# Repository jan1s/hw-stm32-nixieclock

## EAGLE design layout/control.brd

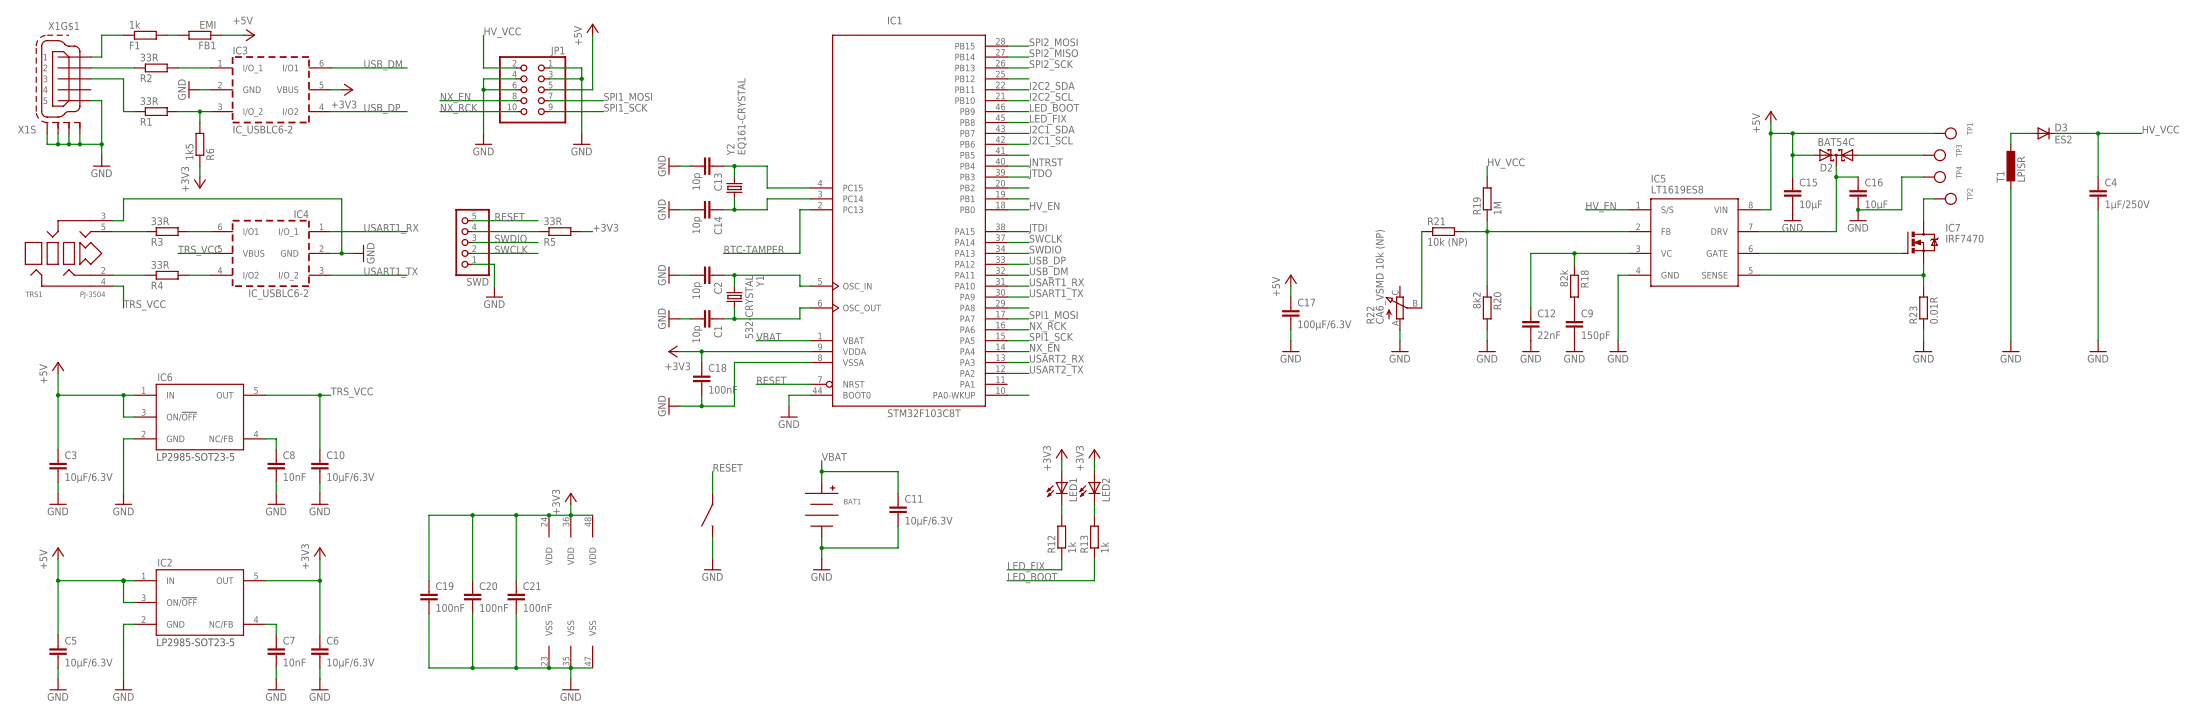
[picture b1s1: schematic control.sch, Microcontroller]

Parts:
BAT1: CR1220-HOLDER; HARWIN-CR1220
C1, C2, C13, C14: 10p; C0603
C3, C5, C6, C10, C11: 10µF/6.3V; C0603
C4: 1µF/250V; C2220K
C7, C8: 10nF; C0603
C9: 150pF; C0603
C12: 22nF; C0603
C15, C16: 10µF; C0603
C17: 100µF/6.3V; C1210
C18, C19, C20, C21: 100nF; C0603
D2: BAT54C; SOT23
D3: ES2; DO-214AA
F1: 1k; R0603
FB1: EMI; R0603
IC1: STM32F103C8T; LQFP48
IC2, IC6: LP2985-SOT23-5; SOT23-5
IC3, IC4: IC_USBLC6-2; SOT-23-6L
IC5: LT1619ES8; SO8
IC7: IRF7470; SO8
ISP: TACT-SWITCH-40-40; 40-40
JP1: PINHD-2X5_2.54-SMD; 2X05SMD
LED1, LED2: LEDCHIP-LED0603; CHIP-LED0603
R1, R2, R3, R4, R5: 33R; R0603
R6: 1k5; R0603
R12, R13: 1k; R0603
R18: 82k; R0603
R19: 1M; M1206
R20: 8k2; R0603
R21: 10k (NP); R0603
R22: CA6_VSMD 10k (NP); CA6-VSMD
R23: 0.01R; R1206
SWD: HEADER-1X5ROUND; 1X05_ROUND
T1: LPISR; PISR
TP1, TP2, TP3, TP4: TESTPOINTROUND2MM; TESTPOINT_ROUND_2MM
TRS1: PJ-3504; YD-PJ-3504
X1: MINI-USB-SCHIELD-32005-201; 32005-201
Y1: 532-CRYSTAL; 2PIN50X32
Y2: EQ161-CRYSTAL; EQ161

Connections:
+3V3: C6.1, C18.1, C19.1, C20.1, C21.1, IC1.9 (VDDA), IC1.24 (VDD), IC1.36 (VDD), IC1.48 (VDD), IC2.5 (OUT), IC3.5 (VBUS), LED1.A, LED2.A, R5.2, R6.1
+5V: C3.1, C5.1, C15.1, C17.1, D2.2 (A2), FB1.1, IC2.1 (IN), IC2.3 (ON/!OFF), IC5.8 (VIN), IC6.1 (IN), IC6.3 (ON/!OFF), JP1.5, TP1.P$1
ASDAWJIODJA: R5.1, SWD.4
GND: BAT1.NEG, C1.2, C2.2, C3.2, C4.2, C5.2, C6.2, C7.2, C8.2, C9.2, C10.2, C11.2, C12.2, C13.2, C14.2, C15.2, C16.2, C17.2, C18.2, C19.2, C20.2, C21.2, IC1.8 (VSSA), IC1.23 (VSS), IC1.35 (VSS), IC1.44 (BOOT0), IC1.47 (VSS), IC2.2 (GND), IC3.2 (GND), IC4.2 (GND), IC5.4 (GND), IC6.2 (GND), ISP.1, ISP.2, JP1.1, JP1.3, JP1.4, JP1.6, R20.2, R22.A, R23.1, SWD.1, T1.P$2 (2), TP4.P$1, TRS1.3, X1.5, X1.M1 (S1), X1.M2 (S2), X1.M3 (S3), X1.M4 (S4)
HV_EN: IC1.18 (PB0), IC5.1 (S/S)
HV_VCC: C4.1, D3.C, JP1.2, R19.2
I2C1_SCL: IC1.42 (PB6)
I2C1_SDA: IC1.43 (PB7)
I2C2_SCL: IC1.21 (PB10)
I2C2_SDA: IC1.22 (PB11)
JNTRST: IC1.40 (PB4)
JTDI: IC1.38 (PA15)
JTDO: IC1.39 (PB3)
LED_BOOT: IC1.46 (PB9), R13.1
LED_FIX: IC1.45 (PB8), R12.1
unnamed: C1.1, IC1.6 (OSC_OUT), Y1.P$1 (1)
unnamed: C2.1, IC1.5 (OSC_IN), Y1.P$2 (2)
unnamed: F1.1, X1.1
unnamed: C8.1, IC6.4 (NC/FB)
unnamed: IC3.3 (I/O_2), R1.2, R6.2
unnamed: IC4.6 (I/O1), R3.2
unnamed: D2.1 (A1), TP3.P$1
unnamed: IC5.6 (GATE), IC7.4 (G)
unnamed: LED2.C, R13.2
unnamed: LED1.C, R12.2
unnamed: R4.1, TRS1.2
unnamed: IC7.5 (D), IC7.6 (D), IC7.7 (D), IC7.8 (D), TP2.P$1
unnamed: C12.1, IC5.3 (VC), R18.1
unnamed: C9.1, R18.2
unnamed: D3.A, T1.P$1 (1)
unnamed: IC5.2 (FB), R19.1, R20.1, R21.2
unnamed: IC5.5 (SENSE), IC7.1 (S), IC7.2 (S), IC7.3 (S), R23.2
unnamed: C16.1, D2.3 (CC), IC5.7 (DRV)
unnamed: C7.1, IC2.4 (NC/FB)
unnamed: R21.1, R22.B (S)
unnamed: F1.2, FB1.2
unnamed: IC3.1 (I/O_1), R2.2
unnamed: R2.1, X1.2
unnamed: IC4.4 (I/O2), R4.2
unnamed: R3.1, TRS1.5
unnamed: C13.1, IC1.4 (PC15), Y2.P$1 (1)
unnamed: C14.1, IC1.3 (PC14), Y2.P$2 (2)
unnamed: R1.1, X1.3
NX_EN: IC1.14 (PA4), JP1.8
NX_RCK: IC1.16 (PA6), JP1.10
RESET: IC1.7 (NRST), ISP.3, ISP.4, SWD.5
RTC-TAMPER: IC1.2 (PC13)
SPI1_MOSI: IC1.17 (PA7), JP1.7
SPI1_SCK: IC1.15 (PA5), JP1.9
SPI2_MISO: IC1.27 (PB14)
SPI2_MOSI: IC1.28 (PB15)
SPI2_SCK: IC1.26 (PB13)
SWCLK: IC1.37 (PA14), SWD.2
SWDIO: IC1.34 (PA13), SWD.3
TRS_VCC: C10.1, IC4.5 (VBUS), IC6.5 (OUT), TRS1.4
USART1_RX: IC1.31 (PA10), IC4.1 (I/O_1)
USART1_TX: IC1.30 (PA9), IC4.3 (I/O_2)
USART2_RX: IC1.13 (PA3)
USART2_TX: IC1.12 (PA2)
USB_DM: IC1.32 (PA11), IC3.6 (I/O1)
USB_DP: IC1.33 (PA12), IC3.4 (I/O2)
VBAT: BAT1.POS, C11.1, IC1.1 (VBAT)

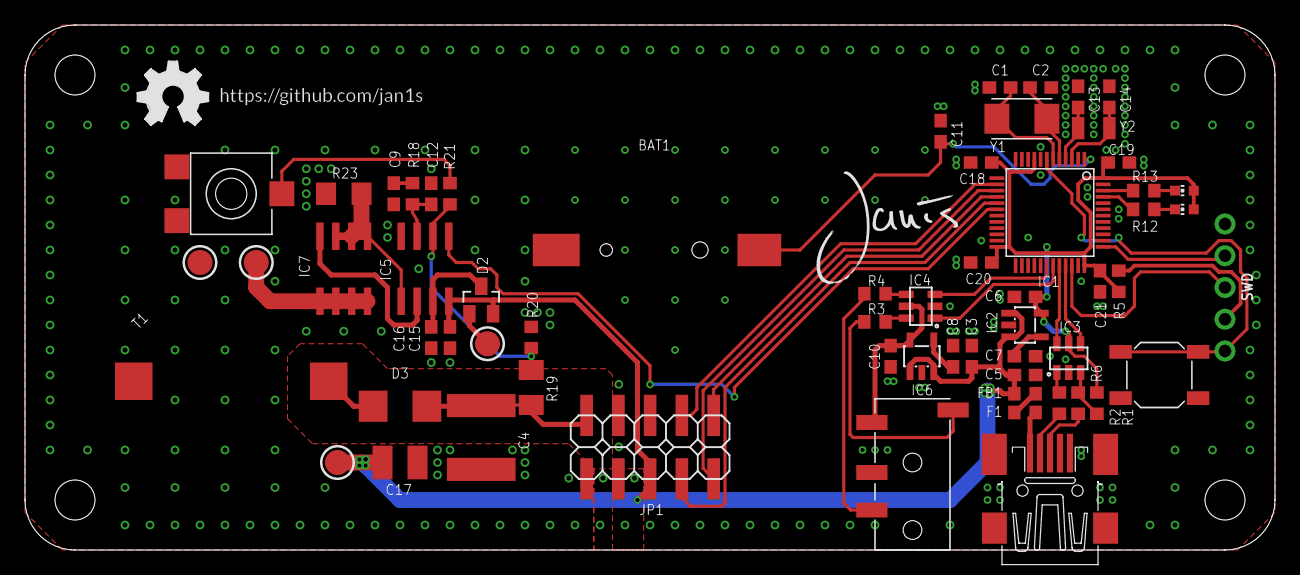
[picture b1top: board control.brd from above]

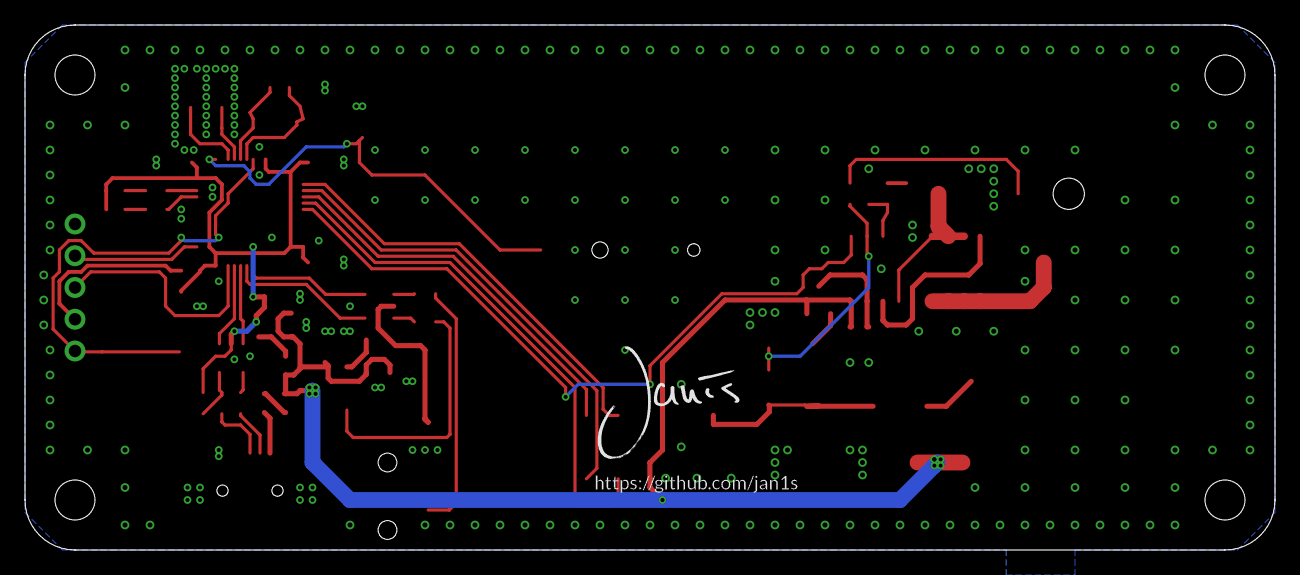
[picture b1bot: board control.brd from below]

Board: 2 copper layers, 100.0 x 42.0 mm, 66 parts (2 on the bottom side), 49 nets.

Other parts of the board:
LOGO1: OSHW_LOGO_FILLX0200-NT; OSHW_FILLX200_NOTEXT
U$1, U$2: JANIS_10MM
U$5, U$6: GITHUB/JAN1S

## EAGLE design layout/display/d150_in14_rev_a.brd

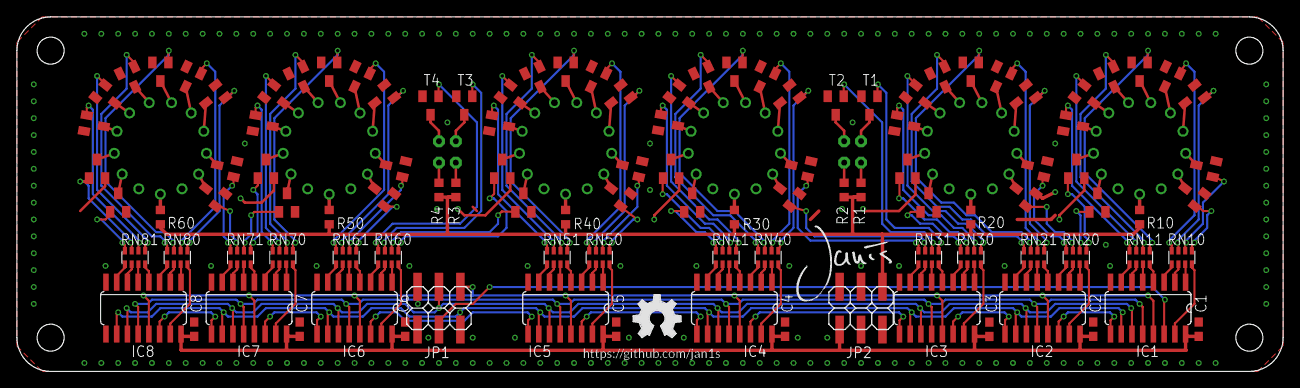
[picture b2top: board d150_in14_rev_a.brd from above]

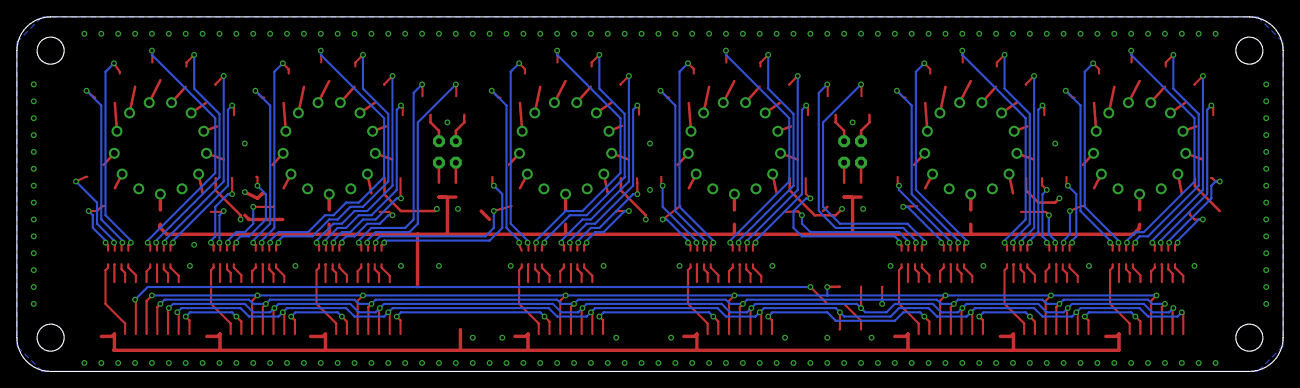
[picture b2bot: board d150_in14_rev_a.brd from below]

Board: 2 copper layers, 150.0 x 42.0 mm, 121 parts (4 on the bottom side), 217 nets.

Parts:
C1, C2, C3, C4, C5, C6, C7, C8: C0603
GL1, GL2, GL3, GL4: NE2-NEON-BULB-DRILL
IC1, IC2, IC3, IC4, IC5, IC6, IC7, IC8: 74HC595D; SO16
JP1, JP2: 2X03SMD
N1: IN-14
R1, R2, R3, R4, R10, R20, R30, R40, R50, R60: R0603
RN10, RN11, RN20, RN21, RN30, RN31, RN40, RN41, RN50, RN51, RN60, RN61, RN70, RN71, RN80, RN81: CTS742C083
T1, T2, T3, T4, T10, T11, T12, T13, T14, T15, T16, T17, T18, T19, T20, T21, T22, T23, T24, T25, T26, T27, T28, T29, T30, T31, T32, T33, T34, T35, T36, T37, T38, T39, T40, T41, T42, T43, T44, T45, T46, T47, T48, T49, T50, T51, T52, T53, T54, T55, T56, T57, T58, T59, T60, T61, T62, T63, T64, T65, T66, T67, T68, T69: SOT23
U$1: OSHW_FILLX200_NOTEXT
U$2: JANIS_10MM
U$3: GITHUB/JAN1S
U$5, U$6, U$7, U$8, U$9: IN-14

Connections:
1A: IC1.15, RN10.4
1B: IC1.1, RN10.3
1C: IC1.2, RN10.2
1D: IC1.3, RN10.1
1E: IC1.4, RN11.4
1F: IC1.5, RN11.3
1G: IC1.6, RN11.2
1H: IC1.7, RN11.1
2A: IC2.15, RN20.4
2B: IC2.1, RN20.3
2B0: RN30.7, T20.1
2B1: RN30.8, T21.1
2B2: RN20.7, T22.1
2B3: RN20.8, T23.1
2B4: RN21.5, T24.1
2B5: RN21.6, T25.1
2B6: RN21.7, T26.1
2B7: RN21.8, T27.1
2B8: RN30.5, T28.1
2B9: RN30.6, T29.1
2C: IC2.2, RN20.2
2D: IC2.3, RN20.1
2E: IC2.4, RN21.4
2F: IC2.5, RN21.3
2G: IC2.6, RN21.2
2H: IC2.7, RN21.1
3A: IC3.15, RN30.4
3B: IC3.1, RN30.3
3B0: RN41.7, T30.1
3B1: RN41.8, T31.1
3B2: RN31.7, T32.1
3B3: RN31.8, T33.1
3B4: RN40.5, T34.1
3B5: RN40.6, T35.1
3B6: RN40.7, T36.1
3B7: RN40.8, T37.1
3B8: RN41.5, T38.1
3B9: RN41.6, T39.1
3C: IC3.2, RN30.2
3D: IC3.3, RN30.1
3E: IC3.4, RN31.4
3F: IC3.5, RN31.3
3G: IC3.6, RN31.2
3H: IC3.7, RN31.1
4A: IC4.15, RN40.4
4B: IC4.1, RN40.3
4B0: RN60.5, T40.1
4B1: RN60.6, T41.1
4B2: RN50.5, T42.1
4B3: RN50.6, T43.1
4B4: RN50.7, T44.1
4B5: RN50.8, T45.1
4B6: RN51.5, T46.1
4B7: RN51.6, T47.1
4B8: RN51.7, T48.1
4B9: RN51.8, T49.1
4C: IC4.2, RN40.2
4D: IC4.3, RN40.1
4E: IC4.4, RN41.4
4F: IC4.5, RN41.3
4G: IC4.6, RN41.2
4H: IC4.7, RN41.1
5A: IC5.15, RN50.4
5B: IC5.1, RN50.3
5B0: RN71.5, T50.1
5B1: RN71.6, T51.1
5B2: RN61.5, T52.1
5B3: RN61.6, T53.1
5B4: RN61.7, T54.1
5B5: RN61.8, T55.1
5B6: RN70.5, T56.1
5B7: RN70.6, T57.1
5B8: RN70.7, T58.1
5B9: RN70.8, T59.1
5C: IC5.2, RN50.2
5D: IC5.3, RN50.1
5E: IC5.4, RN51.4
5F: IC5.5, RN51.3
5G: IC5.6, RN51.2
5H: IC5.7, RN51.1
6A: IC6.15, RN60.4
6B: IC6.1, RN60.3
6B0: RN81.7, T60.1
6B1: RN81.8, T61.1
6B2: RN71.7, T62.1
6B3: RN71.8, T63.1
6B4: RN80.5, T64.1
6B5: RN80.6, T65.1
6B6: RN80.7, T66.1
6B7: RN80.8, T67.1
6B8: RN81.5, T68.1
6B9: RN81.6, T69.1
6C: IC6.2, RN60.2
6D: IC6.3, RN60.1
6E: IC6.4, RN61.4
6F: IC6.5, RN61.3
6G: IC6.6, RN61.2
6H: IC6.7, RN61.1
7A: IC7.15, RN70.4
7B: IC7.1, RN70.3
7C: IC7.2, RN70.2
7D: IC7.3, RN70.1
7E: IC7.4, RN71.4
7F: IC7.5, RN71.3
7G: IC7.6, RN71.2
7H: IC7.7, RN71.1
8A: IC8.15, RN80.4
8B: IC8.1, RN80.3
8C: IC8.2, RN80.2
8D: IC8.3, RN80.1
8E: IC8.4, RN81.4
8F: IC8.5, RN81.3
8G: IC8.6, RN81.2
8H: IC8.7, RN81.1
+5V: C1.1, C2.1, C3.1, C4.1, C5.1, C6.1, C7.1, C8.1, IC1.16, IC2.16, IC3.16, IC4.16, IC5.16, IC6.16, IC7.16, IC8.16, JP2.6
EN: IC1.13, IC2.13, IC3.13, IC4.13, IC5.13, IC6.13, IC7.13, IC8.13, JP1.1
GL1: RN31.5, T1.1
GL2: RN31.6, T2.1
GL3: RN60.7, T3.1
GL4: RN60.8, T4.1
GND: C1.2, C2.2, C3.2, C4.2, C5.2, C6.2, C7.2, C8.2, IC1.8, IC2.8, IC3.8, IC4.8, IC5.8, IC6.8, IC7.8, IC8.8, JP1.6, JP2.2, JP2.3, JP2.4, JP2.5, T1.2, T2.2, T3.2, T4.2, T10.2, T11.2, T12.2, T13.2, T14.2, T15.2, T16.2, T17.2, T18.2, T19.2, T20.2, T21.2, T22.2, T23.2, T24.2, T25.2, T26.2, T27.2, T28.2, T29.2, T30.2, T31.2, T32.2, T33.2, T34.2, T35.2, T36.2, T37.2, T38.2, T39.2, T40.2, T41.2, T42.2, T43.2, T44.2, T45.2, T46.2, T47.2, T48.2, T49.2, T50.2, T51.2, T52.2, T53.2, T54.2, T55.2, T56.2, T57.2, T58.2, T59.2, T60.2, T61.2, T62.2, T63.2, T64.2, T65.2, T66.2, T67.2, T68.2, T69.2
MOSI: IC1.14, JP1.4
N1_B0: RN20.6, T11.1
N1_B1: RN10.5, T12.1
N1_B2: RN10.6, T13.1
N1_B3: RN10.7, T14.1
N1_B4: RN10.8, T15.1
N1_B5: RN11.5, T16.1
N1_B6: RN11.6, T17.1
N1_B7: RN11.7, T18.1
N1_B8: RN11.8, T19.1
N1_B9: RN20.5, T10.1
N1_K0: N1.12, T11.3
N1_K1: N1.3, T12.3
N1_K2: N1.4, T13.3
N1_K3: N1.5, T14.3
N1_K4: N1.6, T15.3
N1_K5: N1.7, T16.3
N1_K6: N1.8, T17.3
N1_K7: N1.9, T18.3
N1_K8: N1.10, T19.3
N1_K9: N1.11, T10.3
N2_0: T22.3, U$5.3
N2_1: T21.3, U$5.12
N2_2: T20.3, U$5.11
N2_3: T29.3, U$5.10
N2_4: T28.3, U$5.9
N2_5: T27.3, U$5.8
N2_6: T26.3, U$5.7
N2_7: T25.3, U$5.6
N2_8: T24.3, U$5.5
N2_9: T23.3, U$5.4
N3_0: T32.3, U$6.3
N3_1: T31.3, U$6.12
N3_2: T30.3, U$6.11
N3_3: T39.3, U$6.10
N3_4: T38.3, U$6.9
N3_5: T37.3, U$6.8
N3_6: T36.3, U$6.7
N3_7: T35.3, U$6.6
N3_8: T34.3, U$6.5
N3_9: T33.3, U$6.4
N4_0: T42.3, U$7.3
N4_1: T41.3, U$7.12
N4_2: T40.3, U$7.11
N4_3: T49.3, U$7.10
N4_4: T48.3, U$7.9
N4_5: T47.3, U$7.8
N4_6: T46.3, U$7.7
N4_7: T45.3, U$7.6
N4_8: T44.3, U$7.5
N4_9: T43.3, U$7.4
N5_0: T52.3, U$8.3
N5_1: T51.3, U$8.12
N5_2: T50.3, U$8.11
N5_3: T59.3, U$8.10
N5_4: T58.3, U$8.9
N5_5: T57.3, U$8.8
N5_6: T56.3, U$8.7
N5_7: T55.3, U$8.6
N5_8: T54.3, U$8.5
N5_9: T53.3, U$8.4
N6_0: T62.3, U$9.3
N6_1: T61.3, U$9.12
N6_2: T60.3, U$9.11
N6_3: T69.3, U$9.10
N6_4: T68.3, U$9.9
N6_5: T67.3, U$9.8
N6_6: T66.3, U$9.7
N6_7: T65.3, U$9.6
N6_8: T64.3, U$9.5
N6_9: T63.3, U$9.4
unnamed: GL2.1, R2.1
unnamed: GL3.1, R3.1
unnamed: GL4.1, R4.1
unnamed: N1.1, R10.1
unnamed: GL2.2, T2.3
unnamed: GL1.2, T1.3
unnamed: GL4.2, T4.3
unnamed: GL3.2, T3.3
unnamed: R20.1, U$5.1
unnamed: IC1.9, IC2.14
unnamed: IC2.9, IC3.14
unnamed: IC3.9, IC4.14
unnamed: R30.1, U$6.1
unnamed: R40.1, U$7.1
unnamed: R60.1, U$9.1
unnamed: IC4.9, IC5.14
unnamed: R50.1, U$8.1
unnamed: IC5.9, IC6.14
unnamed: IC6.9, IC7.14
unnamed: IC7.9, IC8.14
unnamed: GL1.1, R1.1
RCK: IC1.12, IC2.12, IC3.12, IC4.12, IC5.12, IC6.12, IC7.12, IC8.12, JP1.5
SCK: IC1.11, IC2.11, IC3.11, IC4.11, IC5.11, IC6.11, IC7.11, IC8.11, JP1.3
SCL: IC1.10, IC2.10, IC3.10, IC4.10, IC5.10, IC6.10, IC7.10, IC8.10, JP1.2
VDD: JP2.1, R1.2, R2.2, R3.2, R4.2, R10.2, R20.2, R30.2, R40.2, R50.2, R60.2

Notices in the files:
parts and their libraries:
microbuilder: This work is placed in the public domain, and may be freely used for commercial and non-commercial work with the following conditions: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
